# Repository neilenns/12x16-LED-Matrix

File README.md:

# KiBot CI/CD template repository

This repository provides a ready-to-go CI/CD workflow for KiCad with GitHub actions. To use this repo hit the _Use this template_ button then follow the steps from GitHub.

**The repository name must exactly match the name of the KiCad project.
Do not use spaces in either the repository or the project name.**

For everything to work out of the box you should avoid spaces in both the GitHub repository name and the KiCad project name. Use underscores or hyphens instead, for example `TBM930_De-Ice_-_Panel` or `Collins-FMS-3000`.

## Features of this repository template

1. Integration with GitHub releases to automatically produce documentation and
   fabrication files on every GitHub release, including automatic date and version
   stamping of schematics and PCBs.
2. KiBot preflighting on every pull request (ERC/DRC checks disabled by default).
3. VSCode dev container and default build task for easy local testing of KiBot scripts.

## Documentation generated

The following documents are generated on every release build:

- Interactive BOM - HTML
- Schematic - PDF
- PCB front copper and explanatory drawings layers - PDF
- PCB back copper and explanatory drawings layers - PDF
- 3D render - STEP
- PCB front - JPEG
- PCB back - JPEG

These documents can also be generated by manually running the `KiBot - Generate documentation` action on GitHub.

## Fabrication files generated

The following fabrication files are generated on every release build:

- JLCPCB gerbers and drill files, with BOM and placement files for SMT service
- PCBWay gerbers and drill files

The fabrication files can also be generated by manually running the `KiBot - Release` action on GitHub.

## How this works

A complete CodeTour is included in this repository that walks through all the components
of how KiBot scripts and GitHub actions work. [Use github.dev to view the CodeTour](https://github.dev/neilenns/KiBot-CICD-Template)!

## Running builds locally

This repository template includes the files necessary to run in a VSCode dev container,
which dramatically reduces the effort required to use KiBot on Windows machines.

Never used VSCode remote containers before on Windows? Here's how to get set up:

1. From a PowerShell install WSL2 with this command: `wsl --install`
2. Install [Visual Studio Code](https://code.visualstudio.com/Download) and Docker Desktop(https://www.docker.com/products/docker-desktop)
3. Install the [Remote Containers](https://marketplace.visualstudio.com/items?itemName=ms-vscode-remote.remote-containers) extension for VSCode

When installing Docker Desktop you may be told you have to enable virtualization in your computer's BIOS. Setting that up
is outside the scope of this readme but isn't hard. Just do a web search for your motherboard for how to enter the BIOS
and what the exact name of the setting is, then turn it on.

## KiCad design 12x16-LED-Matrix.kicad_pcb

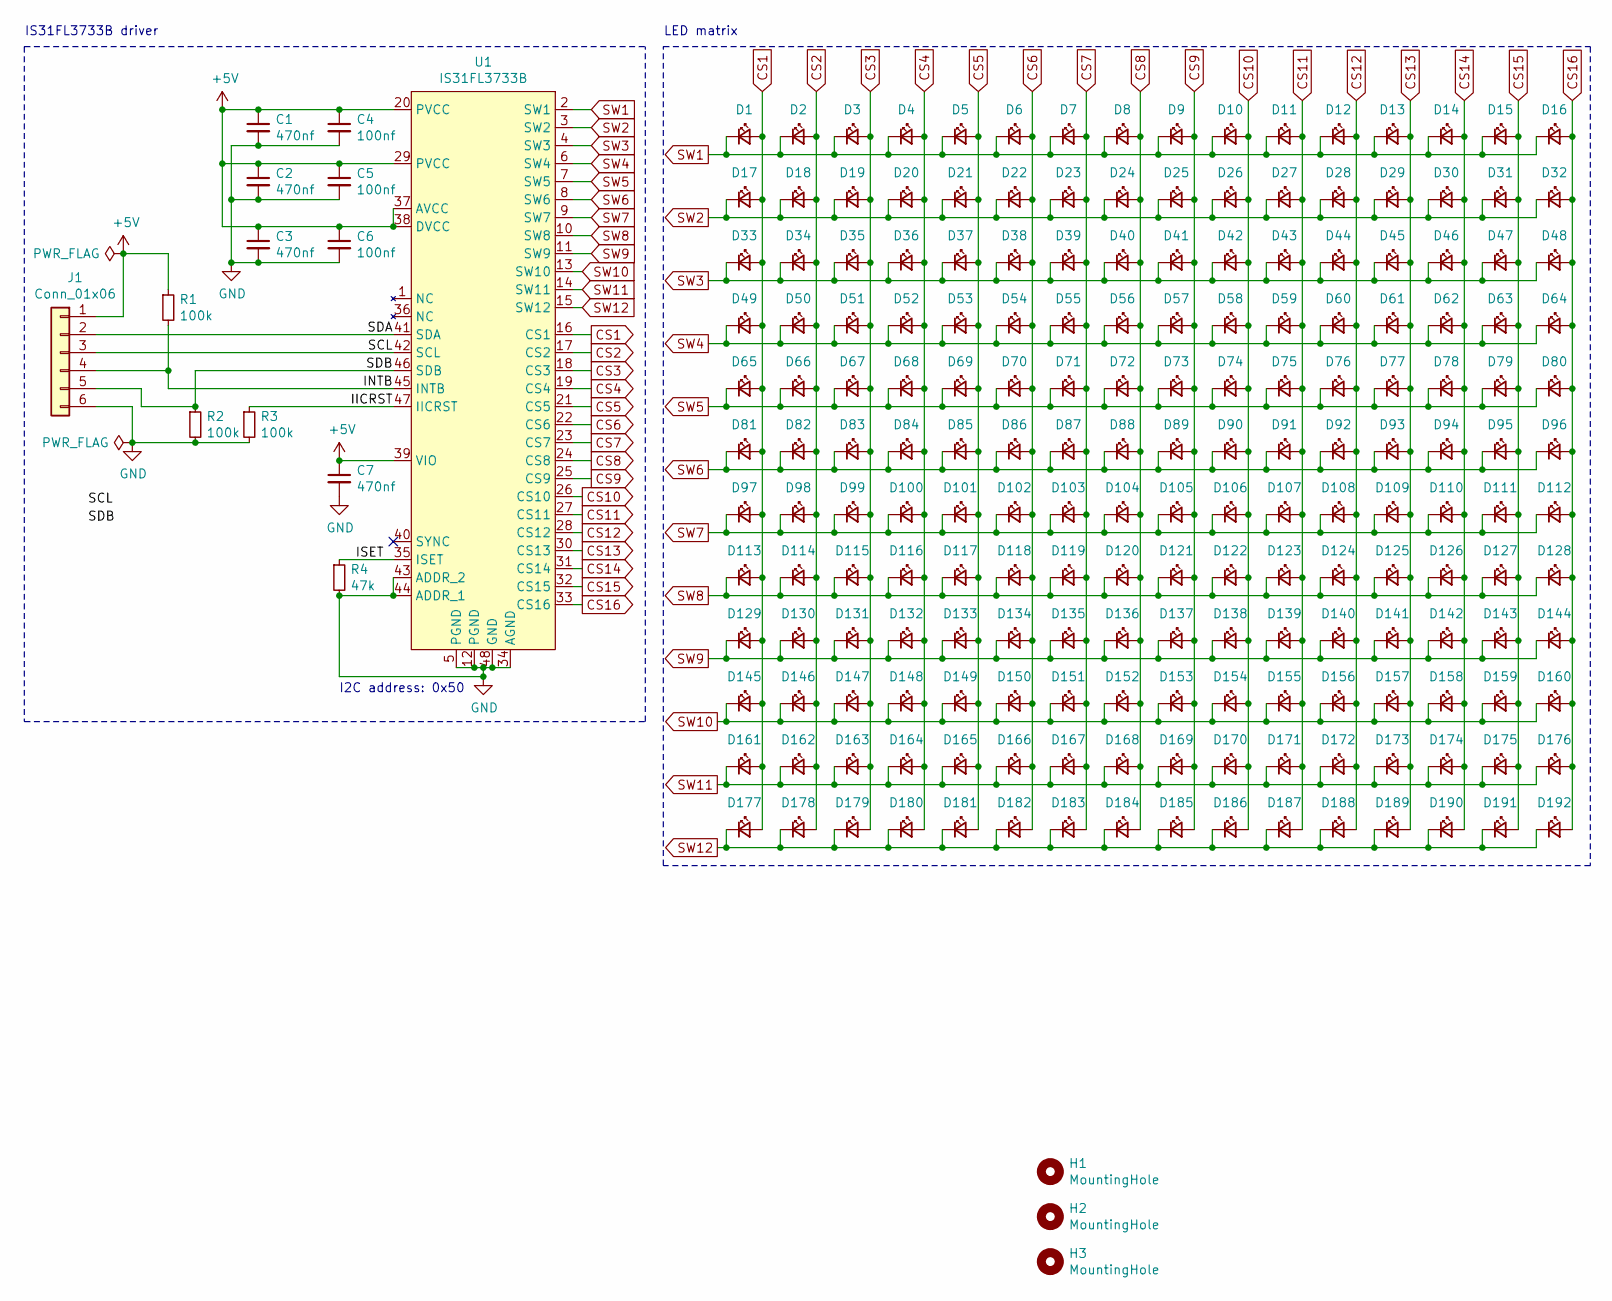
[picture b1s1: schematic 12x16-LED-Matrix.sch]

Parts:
C1, C2, C3, C7: 470nf; C_0402_1005Metric; JLC 0402
C4, C5, C6: 100nf; C_0402_1005Metric; JLC 0402
D1, D2, D3, D4, D5, D6, D7, D8, D9, D10, D11, D12, D13, D14, D15, D16, D17, D18, D19, D20, D21, D22, D23, D24, D25, D26, D27, D28, D29, D30, D31, D32, D33, D34, D35, D36, D37, D38, D39, D40, D41, D42, D43, D44, D45, D46, D47, D48, D49, D50, D51, D52, D53, D54, D55, D56, D57, D58, D59, D60, D61, D62, D63, D64, D65, D66, D67, D68, D69, D70, D71, D72, D73, D74, D75, D76, D77, D78, D79, D80, D81, D82, D83, D84, D85, D86, D87, D88, D89, D90, D91, D92, D93, D94, D95, D96, D97, D98, D99, D100, D101, D102, D103, D104, D105, D106, D107, D108, D109, D110, D111, D112, D113, D114, D115, D116, D117, D118, D119, D120, D121, D122, D123, D124, D125, D126, D127, D128, D129, D130, D131, D132, D133, D134, D135, D136, D137, D138, D139, D140, D141, D142, D143, D144, D145, D146, D147, D148, D149, D150, D151, D152, D153, D154, D155, D156, D157, D158, D159, D160, D161, D162, D163, D164, D165, D166, D167, D168, D169, D170, D171, D172, D173, D174, D175, D176, D177, D178, D179, D180, D181, D182, D183, D184, D185, D186, D187, D188, D189, D190, D191, D192: LED_Small; LED_0603_1608Metric; JLC LED_0603
H1, H2, H3: MountingHole; JLCPCB_Tooling_Hole
J1: Conn_01x06; PinHeader_1x06_P2.54mm_Vertical
R1, R2, R3: 100k; R_0603_1608Metric; JLC 0603
R4: 47k; R_0603_1608Metric; JLC 0603
U1: IS31FL3733B; QFN-48-1EP_6x6mm_P0.4mm_EP4.3x4.3mm_ThermalVias

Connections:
+5V: C1.1, C2.1, C3.1, C4.1, C5.1, C6.1, C7.1, J1.1, R1.1, U1.20 (PVCC), U1.29 (PVCC), U1.37 (AVCC), U1.38 (DVCC), U1.39 (VIO)
/IICRST: R3.1, U1.47 (IICRST)
/INTB: J1.4, R1.2, U1.45 (INTB)
/ISET: R4.1, U1.35 (ISET)
/SCL: J1.3, U1.42 (SCL)
/SDA: J1.2, U1.41 (SDA)
/SDB: J1.5, R2.1, U1.46 (SDB)
CS1: D1.2 (A), D17.2 (A), D33.2 (A), D49.2 (A), D65.2 (A), D81.2 (A), D97.2 (A), D113.2 (A), D129.2 (A), D145.2 (A), D161.2 (A), D177.2 (A), U1.16 (CS1)
CS2: D2.2 (A), D18.2 (A), D34.2 (A), D50.2 (A), D66.2 (A), D82.2 (A), D98.2 (A), D114.2 (A), D130.2 (A), D146.2 (A), D162.2 (A), D178.2 (A), U1.17 (CS2)
CS3: D3.2 (A), D19.2 (A), D35.2 (A), D51.2 (A), D67.2 (A), D83.2 (A), D99.2 (A), D115.2 (A), D131.2 (A), D147.2 (A), D163.2 (A), D179.2 (A), U1.18 (CS3)
CS4: D4.2 (A), D20.2 (A), D36.2 (A), D52.2 (A), D68.2 (A), D84.2 (A), D100.2 (A), D116.2 (A), D132.2 (A), D148.2 (A), D164.2 (A), D180.2 (A), U1.19 (CS4)
CS5: D5.2 (A), D21.2 (A), D37.2 (A), D53.2 (A), D69.2 (A), D85.2 (A), D101.2 (A), D117.2 (A), D133.2 (A), D149.2 (A), D165.2 (A), D181.2 (A), U1.21 (CS5)
CS6: D6.2 (A), D22.2 (A), D38.2 (A), D54.2 (A), D70.2 (A), D86.2 (A), D102.2 (A), D118.2 (A), D134.2 (A), D150.2 (A), D166.2 (A), D182.2 (A), U1.22 (CS6)
CS7: D7.2 (A), D23.2 (A), D39.2 (A), D55.2 (A), D71.2 (A), D87.2 (A), D103.2 (A), D119.2 (A), D135.2 (A), D151.2 (A), D167.2 (A), D183.2 (A), U1.23 (CS7)
CS8: D8.2 (A), D24.2 (A), D40.2 (A), D56.2 (A), D72.2 (A), D88.2 (A), D104.2 (A), D120.2 (A), D136.2 (A), D152.2 (A), D168.2 (A), D184.2 (A), U1.24 (CS8)
CS9: D9.2 (A), D25.2 (A), D41.2 (A), D57.2 (A), D73.2 (A), D89.2 (A), D105.2 (A), D121.2 (A), D137.2 (A), D153.2 (A), D169.2 (A), D185.2 (A), U1.25 (CS9)
CS10: D10.2 (A), D26.2 (A), D42.2 (A), D58.2 (A), D74.2 (A), D90.2 (A), D106.2 (A), D122.2 (A), D138.2 (A), D154.2 (A), D170.2 (A), D186.2 (A), U1.26 (CS10)
CS11: D11.2 (A), D27.2 (A), D43.2 (A), D59.2 (A), D75.2 (A), D91.2 (A), D107.2 (A), D123.2 (A), D139.2 (A), D155.2 (A), D171.2 (A), D187.2 (A), U1.27 (CS11)
CS12: D12.2 (A), D28.2 (A), D44.2 (A), D60.2 (A), D76.2 (A), D92.2 (A), D108.2 (A), D124.2 (A), D140.2 (A), D156.2 (A), D172.2 (A), D188.2 (A), U1.28 (CS12)
CS13: D13.2 (A), D29.2 (A), D45.2 (A), D61.2 (A), D77.2 (A), D93.2 (A), D109.2 (A), D125.2 (A), D141.2 (A), D157.2 (A), D173.2 (A), D189.2 (A), U1.30 (CS13)
CS14: D14.2 (A), D30.2 (A), D46.2 (A), D62.2 (A), D78.2 (A), D94.2 (A), D110.2 (A), D126.2 (A), D142.2 (A), D158.2 (A), D174.2 (A), D190.2 (A), U1.31 (CS14)
CS15: D15.2 (A), D31.2 (A), D47.2 (A), D63.2 (A), D79.2 (A), D95.2 (A), D111.2 (A), D127.2 (A), D143.2 (A), D159.2 (A), D175.2 (A), D191.2 (A), U1.32 (CS15)
CS16: D16.2 (A), D32.2 (A), D48.2 (A), D64.2 (A), D80.2 (A), D96.2 (A), D112.2 (A), D128.2 (A), D144.2 (A), D160.2 (A), D176.2 (A), D192.2 (A), U1.33 (CS16)
GND: C1.2, C2.2, C3.2, C4.2, C5.2, C6.2, C7.2, J1.6, R2.2, R3.2, R4.2, U1.5 (PGND), U1.12 (PGND), U1.34 (AGND), U1.43 (ADDR_2), U1.44 (ADDR_1), U1.48 (GND)
SW1: D1.1 (K), D2.1 (K), D3.1 (K), D4.1 (K), D5.1 (K), D6.1 (K), D7.1 (K), D8.1 (K), D9.1 (K), D10.1 (K), D11.1 (K), D12.1 (K), D13.1 (K), D14.1 (K), D15.1 (K), D16.1 (K), U1.2 (SW1)
SW2: D17.1 (K), D18.1 (K), D19.1 (K), D20.1 (K), D21.1 (K), D22.1 (K), D23.1 (K), D24.1 (K), D25.1 (K), D26.1 (K), D27.1 (K), D28.1 (K), D29.1 (K), D30.1 (K), D31.1 (K), D32.1 (K), U1.3 (SW2)
SW3: D33.1 (K), D34.1 (K), D35.1 (K), D36.1 (K), D37.1 (K), D38.1 (K), D39.1 (K), D40.1 (K), D41.1 (K), D42.1 (K), D43.1 (K), D44.1 (K), D45.1 (K), D46.1 (K), D47.1 (K), D48.1 (K), U1.4 (SW3)
SW4: D49.1 (K), D50.1 (K), D51.1 (K), D52.1 (K), D53.1 (K), D54.1 (K), D55.1 (K), D56.1 (K), D57.1 (K), D58.1 (K), D59.1 (K), D60.1 (K), D61.1 (K), D62.1 (K), D63.1 (K), D64.1 (K), U1.6 (SW4)
SW5: D65.1 (K), D66.1 (K), D67.1 (K), D68.1 (K), D69.1 (K), D70.1 (K), D71.1 (K), D72.1 (K), D73.1 (K), D74.1 (K), D75.1 (K), D76.1 (K), D77.1 (K), D78.1 (K), D79.1 (K), D80.1 (K), U1.7 (SW5)
SW6: D81.1 (K), D82.1 (K), D83.1 (K), D84.1 (K), D85.1 (K), D86.1 (K), D87.1 (K), D88.1 (K), D89.1 (K), D90.1 (K), D91.1 (K), D92.1 (K), D93.1 (K), D94.1 (K), D95.1 (K), D96.1 (K), U1.8 (SW6)
SW7: D97.1 (K), D98.1 (K), D99.1 (K), D100.1 (K), D101.1 (K), D102.1 (K), D103.1 (K), D104.1 (K), D105.1 (K), D106.1 (K), D107.1 (K), D108.1 (K), D109.1 (K), D110.1 (K), D111.1 (K), D112.1 (K), U1.9 (SW7)
SW8: D113.1 (K), D114.1 (K), D115.1 (K), D116.1 (K), D117.1 (K), D118.1 (K), D119.1 (K), D120.1 (K), D121.1 (K), D122.1 (K), D123.1 (K), D124.1 (K), D125.1 (K), D126.1 (K), D127.1 (K), D128.1 (K), U1.10 (SW8)
SW9: D129.1 (K), D130.1 (K), D131.1 (K), D132.1 (K), D133.1 (K), D134.1 (K), D135.1 (K), D136.1 (K), D137.1 (K), D138.1 (K), D139.1 (K), D140.1 (K), D141.1 (K), D142.1 (K), D143.1 (K), D144.1 (K), U1.11 (SW9)
SW10: D145.1 (K), D146.1 (K), D147.1 (K), D148.1 (K), D149.1 (K), D150.1 (K), D151.1 (K), D152.1 (K), D153.1 (K), D154.1 (K), D155.1 (K), D156.1 (K), D157.1 (K), D158.1 (K), D159.1 (K), D160.1 (K), U1.13 (SW10)
SW11: D161.1 (K), D162.1 (K), D163.1 (K), D164.1 (K), D165.1 (K), D166.1 (K), D167.1 (K), D168.1 (K), D169.1 (K), D170.1 (K), D171.1 (K), D172.1 (K), D173.1 (K), D174.1 (K), D175.1 (K), D176.1 (K), U1.14 (SW11)
SW12: D177.1 (K), D178.1 (K), D179.1 (K), D180.1 (K), D181.1 (K), D182.1 (K), D183.1 (K), D184.1 (K), D185.1 (K), D186.1 (K), D187.1 (K), D188.1 (K), D189.1 (K), D190.1 (K), D191.1 (K), D192.1 (K), U1.15 (SW12)

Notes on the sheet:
IS31FL3733B driver
LED matrix
I2C address: 0x50

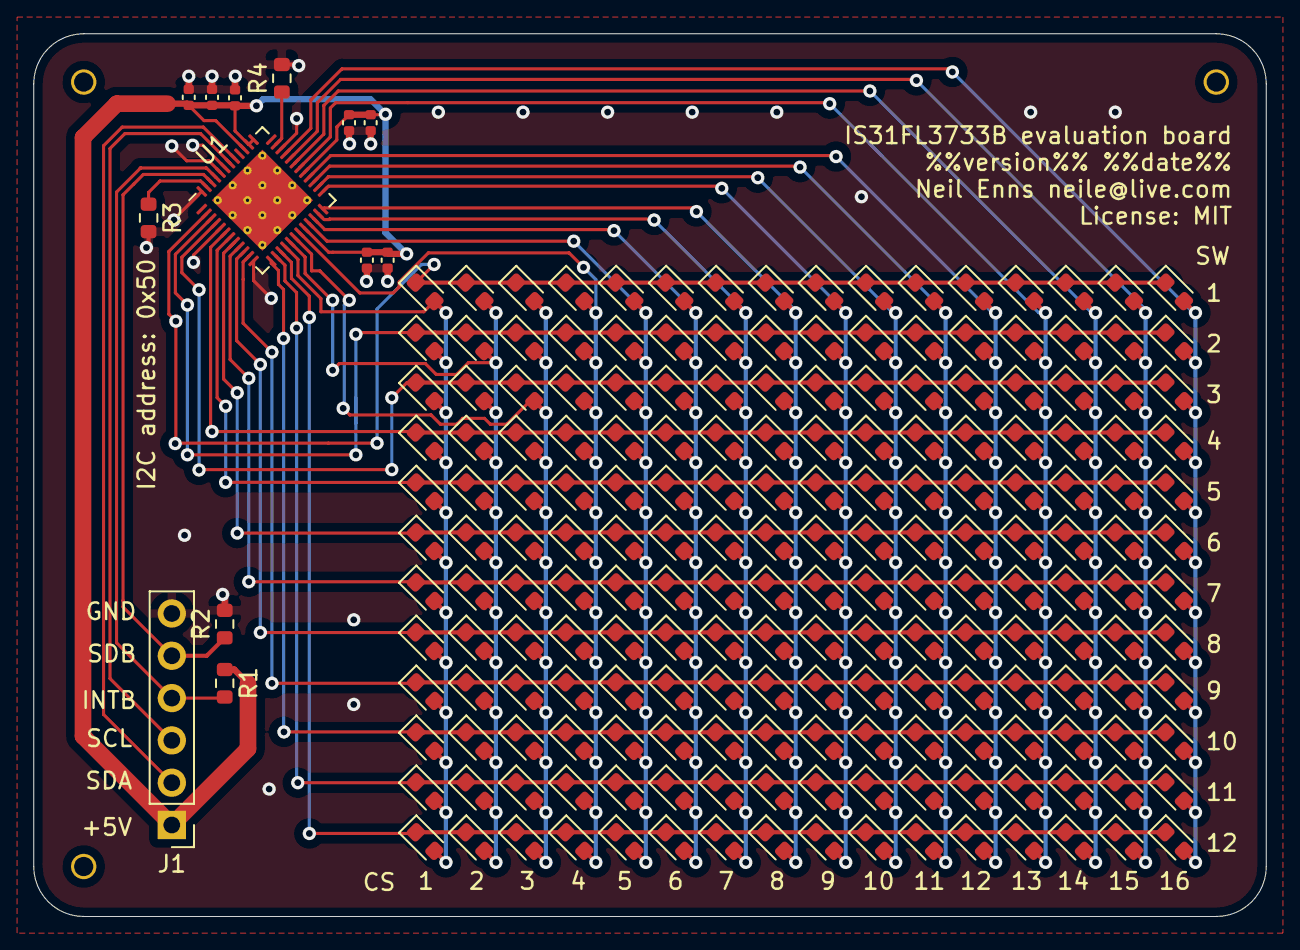
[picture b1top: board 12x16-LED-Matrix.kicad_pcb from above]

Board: 2 copper layers, 74.0 x 53.0 mm, 208 parts (0 on the bottom side), 36 nets.

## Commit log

2021-11-12 Full version
2021-11-12 Fix JLCPCB rotation (even though it isn't used in this repo)
2021-11-12 Add silkscreen
2021-11-12 Update JLCPCB script
2021-11-12 Add ground pins, fix silkscreen
2021-11-26 Add driver directly to schematic
2021-11-26 Move all LED references to the fab layer
2021-11-26 Fully routed board
2021-11-26 Update release action
2021-11-28 Switch to 47k ISET resistor
2021-12-06 Update components based on JLCPCB availability
2021-12-07 Added some via stitching
2025-02-25 Add renovate.json

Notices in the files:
12x16-LED-Matrix.kicad_pcb:
License: MIT
